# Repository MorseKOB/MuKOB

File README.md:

# MuKOB (μKOB) - Micro-controller based MorseKOB Client Device

Raspberry Pi Pico W (RP2040 CPU) based device with a built-in display and
a terminal interface. Uses built-in wifi to connect to the MorseKOB Server.

It interfaces to a KOB, Key + Sounder, Key + Tone, Paddle + Tone, etc. to provide Morse
input and output. The device can operate completely stand-alone (using the
display-touchscreen) or it can connect to a VT-220 terminal (or emulator like Putty)
to provide a larger interface and allow keyboard input.

It supports both American (railroad) and International code with sounder or tone
output, and allows use of Farnsworth word/character timing to promote improving
copying speed.

This repo also includes the **MuKOB Interface** which can be used with **MKOB** and **MorseKOB** through a USB to a PC.

# References
* [MorseKOB Main Project](https://github.com/MorseKOB)
* [PyKOB - The full/computer MKOB Client Application, utilities and Python libraries](https://github.com/MorseKOB/PyKOB)
* [Raspberry Pi Pico W](https://www.raspberrypi.com/documentation/microcontrollers/raspberry-pi-pico.html)
* [FatFs - Generic FAT Filesystem Module](http://elm-chan.org/fsw/ff/00index_e.html)
* [no-OS-FatFS-SD-SPI-RPi-Pico](https://github.com/carlk3/no-OS-FatFS-SD-SPI-RPi-Pico)

# Acknowledgements
The first, and probably most significant acknowledgement has to go to the architects, developers, technical writers, and other staff members responsible for the **Raspberry Pi Pico** and **Pico W**, the **Raspberry Pi Pico C/C++ SDK**, and the **Raspberry Pi Pico C/C++ Samples**.

This application implements a 'C' version of the American Morse encoding and decoding algorithms developed by *Les Kerr*.

The FAT file system and SD card libraries, with some small modifications (to configure for the MuKOB board and remove some printing), are from *ChaN* and *Carl Kugler* respectively.

As with every significant C project I've undertaken since the early '80s, my 'go-to' reference is **The C Programming Language** by *Brian Kernighan* and *Dennis Ritchie* (Prentice Hall, 1978 & 1988).

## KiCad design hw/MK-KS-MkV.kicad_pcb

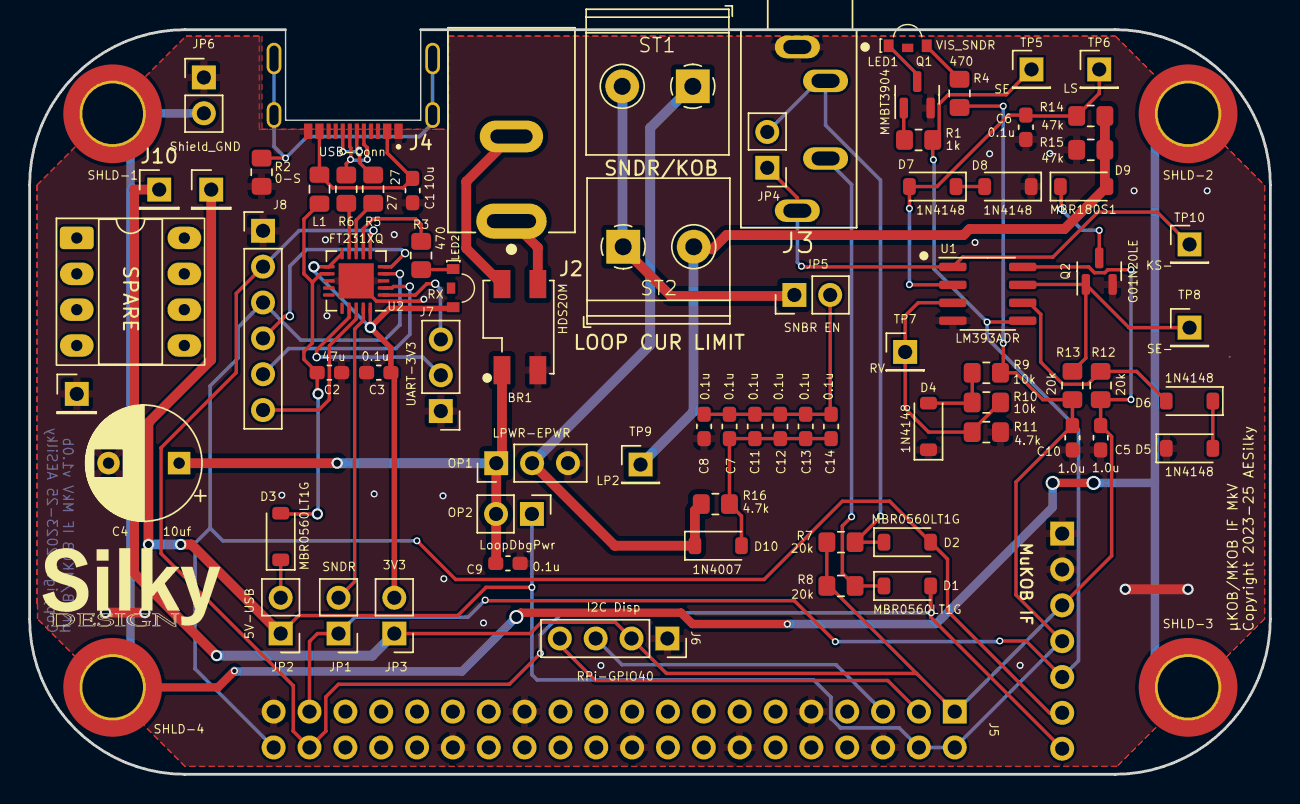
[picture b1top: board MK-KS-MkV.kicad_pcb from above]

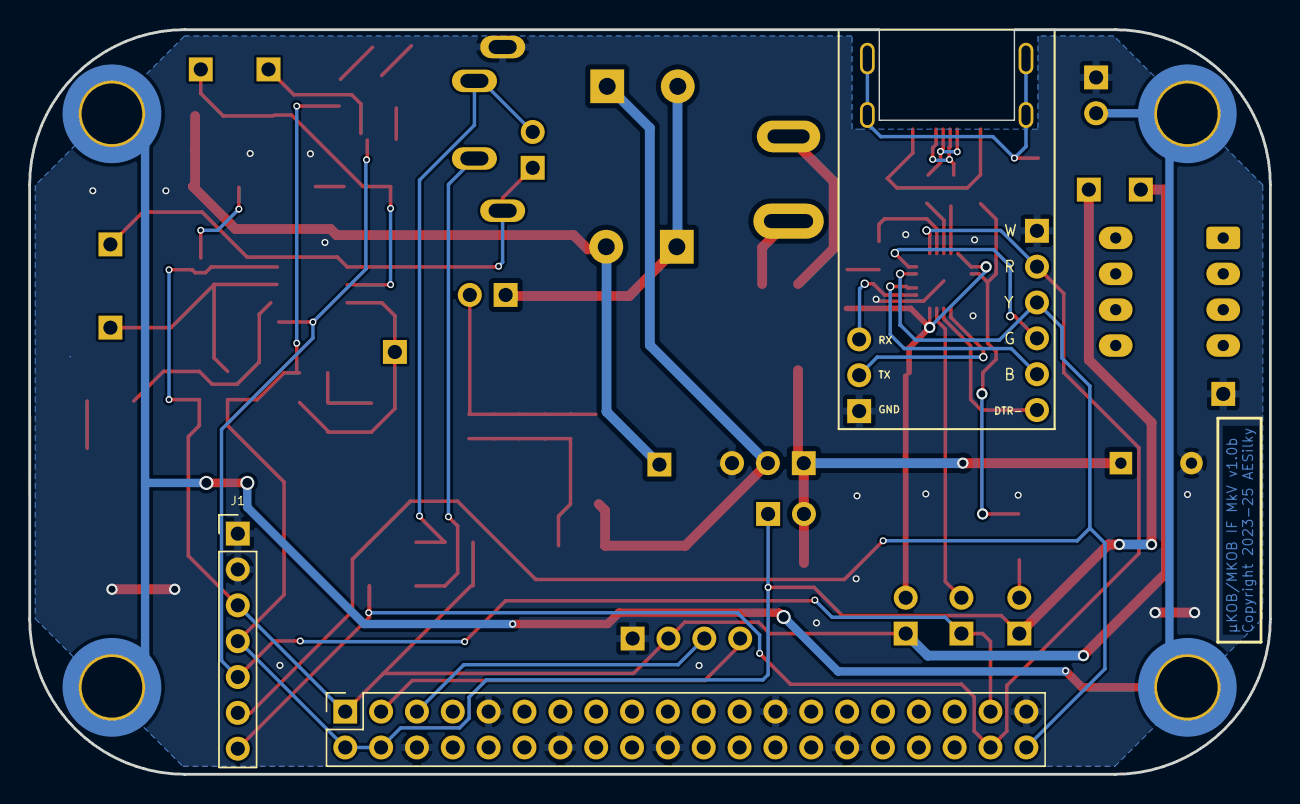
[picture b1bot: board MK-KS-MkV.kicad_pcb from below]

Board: 2 copper layers, 87.9 x 52.8 mm, 79 parts (2 on the bottom side), 48 nets.

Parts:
BR1: HDS20M; AES-BridgeRect-HDS20M-13-1KV-2A
C1: 10u; C_0603_1608Metric_Pad1.08x0.95mm_HandSolder
C2: 47u; C_0603_1608Metric_Pad1.08x0.95mm_HandSolder
C3, C6, C7, C8, C9, C11, C12, C13, C14: 0.1u; C_0603_1608Metric_Pad1.08x0.95mm_HandSolder
C4: 10uf; CP_Radial_D8.0mm_P5.00mm
C5, C10: 1.0u; C_0603_1608Metric_Pad1.08x0.95mm_HandSolder
D1, D2, D3: MBR0560LT1G; D_SOD-123
D4, D5, D6, D7, D8: 1N4148; D_SOD-123
D9: MBR180S1; D_SOD-123
D10: 1N4007; D_SOD-123
J1: MuKOB IF; PinHeader_1x07_P2.54mm_Vertical
J2: LOOP PWR; AES-CUI_PJ-037B
J3: KEY-PADDLE-1_8; AES-CUI_SJ1-3534NG-audio-jack
J4: USB-Conn; AES-USB_C_Amphenol_GSB1C4621DSHR
J5: RPi-GPIO40; PinSocket_2x20_P2.54mm_Vertical
J6: I2C Disp; PinSocket_1x04_P2.54mm_Vertical
J7: UART-3V3; PinHeader_1x03_P2.54mm_Vertical
J8: Selector-SW; PinHeader_1x06_P2.54mm_Vertical
J9, J10, J11: HDR 1x01 Pin; PinHeader_1x01_P2.54mm_Vertical
JP1: SNDR; PinHeader_1x02_P2.54mm_Vertical
JP2: 5V-USB; PinHeader_1x02_P2.54mm_Vertical
JP3: 3V3; PinHeader_1x02_P2.54mm_Vertical
JP4: KeyJack-NP; PinHeader_1x02_P2.54mm_Vertical
JP5: SNBR EN; PinHeader_1x02_P2.54mm_Vertical
JP6: Shield_GND; PinHeader_1x02_P2.54mm_Vertical
L1: 600RJ0.5A; L_0805_2012Metric_Pad1.15x1.40mm_HandSolder
LED1: VIS_SNDR; AES-LED_SMD_SIDEVIEW_Harvatek
LED2: RX; AES-LED_SMD_SIDEVIEW_Harvatek
OP1: LPWR-EPWR; PinHeader_1x03_P2.54mm_Vertical
OP2: LoopDbgPwr; PinHeader_1x02_P2.54mm_Vertical
Q1: MMBT3904; SOT-23
Q2: G01N20LE; SOT-23
R1: 1k; R_0805_2012Metric_Pad1.20x1.40mm_HandSolder
R2: 0-S; R_0805_2012Metric_Pad1.20x1.40mm_HandSolder
R3, R4: 470; R_0805_2012Metric_Pad1.20x1.40mm_HandSolder
R5, R6: 27; R_0805_2012Metric_Pad1.20x1.40mm_HandSolder
R7, R8, R12, R13: 20k; R_0805_2012Metric_Pad1.20x1.40mm_HandSolder
R9, R10: 10k; R_0805_2012Metric_Pad1.20x1.40mm_HandSolder
R11, R16: 4.7k; R_0805_2012Metric_Pad1.20x1.40mm_HandSolder
R14, R15: 47k; R_0805_2012Metric_Pad1.20x1.40mm_HandSolder
SHLD-1, SHLD-2, SHLD-3, SHLD-4: MountingHole_Pad; MountingHole_4.3mm_M4_ISO14580_Pad_TopBottom
ST1: SNDR/KOB; AES-TermBlock-2POS-5mm-Horz
ST2: LOOP CUR LIMIT; AES-TermBlock-2POS-5mm-Horz
TP5: SE; PinHeader_1x01_P2.54mm_Vertical
TP6: LS; PinHeader_1x01_P2.54mm_Vertical
TP7: RV; PinHeader_1x01_P2.54mm_Vertical
TP8: SE-; PinHeader_1x01_P2.54mm_Vertical
TP9: LP2; PinHeader_1x01_P2.54mm_Vertical
TP10: KS-; PinHeader_1x01_P2.54mm_Vertical
U1: LM393ADR; SOIC-8_3.9x4.9mm_P1.27mm
U2: FT231XQ; QFN-20-1EP_4x4mm_P0.5mm_EP2.5x2.5mm

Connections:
+3.3V: C5.2, J1.3, J5.1 (P3V3), J6.2, J10.1, JP3.1 (A), R7.2, R8.2, R12.1, U1.8 (VCC)
+5V: C10.2, J1.4, J5.2 (P5V), J5.4 (P5V), J9.1, JP2.1 (A), OP2.1, R4.1, R9.2, R13.2
/DASH-: D1.2 (A), J1.7, J5.38 (BCM20), J8.2, U2.6 (~CTS)
/DCD-: J8.4, U2.5 (~DCD)
/DOT-: D2.2 (A), J1.6, J5.40 (BCM21), J8.3, U2.4 (~DSR)
/DTR-: J8.6, U2.18 (~DTR)
/KEY_PDL_DOT-: D2.1 (K), J3.2, JP4.2 (B), R7.1
/KOB_KEY-: J3.4, JP4.1 (A), TP10.1, U1.1 (1OUT)
/LOOP_PWR: D10.1 (K), OP1.2 (C), R16.1, ST1.1
/LOOP_STATE: C6.1, D7.2 (A), R14.2, TP6.1, U1.2
/LP1: JP5.1 (A), ST1.2, ST2.1
/LP2: D9.2 (A), R14.1, R15.2, ST2.2, TP9.1
/LPI_A: BR1.4 (A), J2.1 (In)
/LPI_B: BR1.2 (A), J2.2 (Ext)
/LPI_P: BR1.1 (+), C4.1, C9.1, OP1.1 (A), OP2.2
/OFFSET_REF_V: R10.1, R11.2, TP7.1, U1.3
/PDL_DASH-: D1.1 (K), J3.3, R8.1
/RI-: J8.5, U2.2 (~RI)
/RTS: JP1.2 (B), U2.19 (~RTS)
/SCL: J5.5 (BCM3), J6.3
/SDA: J5.3 (BCM2), J6.4
/SNDR_EN: J1.5, J5.37 (BCM26), JP1.1 (A), R1.1, TP5.1, U1.5 (2IN+)
/SNDR_EN-: Q2.1 (G), R13.1, TP8.1, U1.7 (2OUT)
/V3.3I: C3.1, JP3.2 (B), LED2.2 (A), U2.10 (3V3OUT), U2.11 (~RESET), U2.20 (VCCIO)
/V5I: C2.2, D3.2 (A), L1.2, U2.12 (VCC)
Earth: JP6.2 (B), SHLD-1.1, SHLD-2.1, SHLD-3.1, SHLD-4.1
GND: BR1.3 (-), C1.1, C2.1, C3.2, C4.2, C5.1, C6.2, C8.2, C9.2, C10.1, D4.1 (K), D5.1 (K), D8.1 (K), J1.1, J1.2, J3.1, J4.A1_B12 (GND), J4.B1_A12 (GND), J5.6 (GND), J5.9 (GND), J5.14 (GND), J5.20 (GND), J5.25 (GND), J5.30 (GND), J5.39 (GND), J6.1, J7.1, J8.1, J11.1, JP6.1 (A), OP1.3 (B), Q1.2 (E), Q2.2 (S), R2.1, R11.1, R15.1, U1.4 (GND), U2.3 (GND), U2.13 (GND), U2.21 (GND)
unnamed: C1.2, J4.A4_B9 (VBUS), J4.B4_A9 (VBUS), L1.1
unnamed: D3.1 (K), JP2.2 (B)
unnamed: D4.2 (A), R9.1, R10.2
unnamed: D5.2 (A), D6.1 (K)
unnamed: D6.2 (A), R12.2, U1.6 (2IN-)
unnamed: D7.1 (K), D8.2 (A)
unnamed: D9.1 (K), Q2.3 (D)
unnamed: C7.1, C11.1, C12.1, C13.1, C14.1, D10.2 (A), R16.2
unnamed: J4.A6 (D+), J4.B6 (D+), R5.1
unnamed: J4.A7 (D-), J4.B7 (D-), R6.1
unnamed: J4.SH1 (SHIELD), J4.SH2 (SHIELD), J4.SH3 (SHIELD), J4.SH4 (SHIELD), R2.2
unnamed: J7.2, U2.17 (TXD)
unnamed: J7.3, U2.1 (RXD)
unnamed: C7.2, C8.1, C11.2, C12.2, C13.2, C14.2, JP5.2 (B)
unnamed: LED1.2 (A), R4.2
unnamed: LED1.1 (K), Q1.3 (C)
unnamed: LED2.1 (K), R3.1
unnamed: Q1.1 (B), R1.2
unnamed: R3.2, U2.7 (CBUS2)
unnamed: R6.2, U2.9 (USBDM)
unnamed: R5.2, U2.8 (USBDP)

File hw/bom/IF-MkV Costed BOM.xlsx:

Item | Sourced | Placed | References | Value | Footprint | Quantity Total | Cost Each | Base | Base Cost | Key Jack 1/8 | K18 Cost | Sndr/Loop Power | SLPS Cost | LED (Vis) Sounder | L(VS) Cost | RPi Conn | RPC Cost | Debug Only | (qty check)
1 |  |  | C3, C6, C7, C8, C9, C11, C12, C13, C14 | 0.1u | C_0603_1608Metric_Pad1.08x0.95mm_HandSolder | 9 | 0.02 | 8 | 0.16 |  | 0 | 1 | 0.02 |  | 0 | -1 | -0.02 |  | 9
2 |  |  | C5, C10 | 1.0u | C_0603_1608Metric_Pad1.08x0.95mm_HandSolder | 2 | 0.02 | 2 | 0.04 |  | 0 |  | 0 |  | 0 |  | 0 |  | 2
3 |  |  | C1 | 10u | C_0603_1608Metric_Pad1.08x0.95mm_HandSolder | 1 | 0.02 | 1 | 0.02 |  | 0 |  | 0 |  | 0 | -1 | -0.02 |  | 1
4 |  |  | C2 | 47u | C_0603_1608Metric_Pad1.08x0.95mm_HandSolder | 1 | 0.05 | 1 | 0.05 |  | 0 |  | 0 |  | 0 | -1 | -0.05 |  | 1
5 |  |  | C4 | 10uf | CP_Radial_D8.0mm_P5.00mm | 1 | 1.5 | 0 | 0 |  | 0 | 1 | 1.5 |  | 0 |  | 0 |  | 1
6 |  |  | R7, R8, R12, R13 | 20k | R_0805_2012Metric_Pad1.20x1.40mm_HandSolder | 4 | 0.03 | 4 | 0.12 |  | 0 |  | 0 |  | 0 |  | 0 |  | 4
7 |  |  | R3, R4 | 470 | R_0805_2012Metric_Pad1.20x1.40mm_HandSolder | 1 | 0.03 | 0 | 0 |  | 0 |  | 0 | 1 | 0.03 |  | 0 |  | 1
8 |  |  | R5, R6 | 27 | R_0805_2012Metric_Pad1.20x1.40mm_HandSolder | 2 | 0.03 | 2 | 0.06 |  | 0 |  | 0 |  | 0 | -2 | -0.06 |  | 2
9 |  |  | R9, R10 | 10k | R_0805_2012Metric_Pad1.20x1.40mm_HandSolder | 2 | 0.03 | 2 | 0.06 |  | 0 |  | 0 |  | 0 |  | 0 |  | 2
10 |  |  | R11, R16 | 4.7k | R_0805_2012Metric_Pad1.20x1.40mm_HandSolder | 2 | 0.03 | 2 | 0.06 |  | 0 |  | 0 |  | 0 |  | 0 |  | 2
11 |  |  | R14, R15 | 47k | R_0805_2012Metric_Pad1.20x1.40mm_HandSolder | 2 | 0.03 | 2 | 0.06 |  | 0 |  | 0 |  | 0 |  | 0 |  | 2
12 |  |  | R1 | 1k | R_0805_2012Metric_Pad1.20x1.40mm_HandSolder | 1 | 0.03 | 0 | 0 |  | 0 |  | 0 | 1 | 0.03 |  | 0 |  | 1
13 |  |  | R2 | 0-S | R_0805_2012Metric_Pad1.20x1.40mm_HandSolder | 1 | 0.03 | 1 | 0.03 |  | 0 |  | 0 |  | 0 | -1 | -0.03 |  | 1
14 |  |  | L1 | 600RJ0.5A | L_0805_2012Metric_Pad1.15x1.40mm_HandSolder | 1 | 0.15 | 1 | 0.15 |  | 0 |  | 0 |  | 0 |  | 0 |  | 1
15 |  |  | D4, D5, D6, D7, D8 | 1N4148 | D_SOD-123 | 5 | 0.05 | 5 | 0.25 |  | 0 |  | 0 |  | 0 |  | 0 |  | 5
16 |  |  | D1, D2, D3 | MBR0560LT1G | D_SOD-123 | 3 | 0.15 | 3 | 0.44999999999999996 |  | 0 |  | 0 |  | 0 |  | 0 |  | 3
17 |  |  | D9 | MBR180S1 | D_SOD-123 | 1 | 0.15 | 1 | 0.15 |  | 0 |  | 0 |  | 0 |  | 0 |  | 1
18 |  |  | D10 | 1N4007 | D_SOD-123 | 1 | 0.08 | 1 | 0.08 |  | 0 |  | 0 |  | 0 |  | 0 |  | 1
19 |  |  | U1 | LM393ADR | SOIC-8_3.9x4.9mm_P1.27mm | 1 | 0.5 | 1 | 0.5 |  | 0 |  | 0 |  | 0 |  | 0 |  | 1
20 |  |  | U2 | FT231XQ | QFN-20-1EP_4x4mm_P0.5mm_EP2.5x2.5mm | 1 | 3.5 | 1 | 3.5 |  | 0 |  | 0 |  | 0 | -1 | -3.5 |  | 1
21 |  |  | BR1 | HDS20M | AES-BridgeRect-HDS20M-13-1KV-2A | 1 | 0.3 | 0 | 0 |  | 0 | 1 | 0.3 |  | 0 |  | 0 |  | 1
22 |  |  | JP4 | KeyJack-NP | PinHeader_1x02_P2.54mm_Vertical | 1 | 0.01 | 1 | 0.01 |  | 0 |  | 0 |  | 0 |  | 0 |  | 1
23 |  |  | JP5 | SNBR EN | PinHeader_1x02_P2.54mm_Vertical | 1 | 0.01 | 1 | 0.01 |  | 0 |  | 0 |  | 0 |  | 0 |  | 1
24 |  |  | JP6 | Shield-GND | PinHeader_1x02_P2.54mm_Vertical | 1 | 0.01 | 1 | 0.01 |  | 0 |  | 0 |  | 0 |  | 0 |  | 1
25 |  |  | LED1 | VIS_SNDR | AES-LED_SMD_SIDEVIEW_Harvatek | 1 | 0.1 | 0 | 0 |  | 0 |  | 0 | 1 | 0.1 |  | 0 |  | 1
26 |  |  | LED2 | RX | AES-LED_SMD_SIDEVIEW_Harvatek | 0 | 0.1 | 0 | 0 |  | 0 |  | 0 |  | 0 |  | 0 |  | 0
27 |  |  | OP1 | LPWR-EPWR | PinHeader_1x03_P2.54mm_Vertical | 1 | 0.03 | 0 | 0 |  | 0 | 1 | 0.03 |  | 0 |  | 0 |  | 1
28 |  |  | Q1 | MMBT3904 | SOT-23 | 1 | 0.04 | 0 | 0 |  | 0 |  | 0 | 1 | 0.04 |  | 0 |  | 1
29 |  |  | Q2 | G01N20LE | SOT-23 | 1 | 0.35 | 1 | 0.35 |  | 0 |  | 0 |  | 0 |  | 0 |  | 1
30 |  |  | ST1 | SNDR/KOB | AES-TermBlock-2POS-5mm-Horz | 1 | 0.35 | 1 | 0.35 |  | 0 |  | 0 |  | 0 |  | 0 |  | 1
31 |  |  | ST2 | LOOP CUR LIMIT | AES-TermBlock-2POS-5mm-Horz | 1 | 0.35 | 1 | 0.35 |  | 0 |  | 0 |  | 0 |  | 0 |  | 1
32 |  |  | J2 | LOOP PWR | AES-CUI_PJ-037B | 1 | 0.7 | 0 | 0 |  | 0 | 1 | 0.7 |  | 0 |  | 0 |  | 1
33 |  |  | J3 | KEY-PADDLE-1_8 | AES-CUI_SJ1-3534NG-audio-jack | 1 | 1.5 | 0 | 0 | 1 | 1.5 |  | 0 |  | 0 |  | 0 |  | 1
34 |  |  | J4 | USB-Conn | AES-USB_C_Amphenol_GSB1C4621DSHR | 1 | 0.5 | 1 | 0.5 |  | 0 |  | 0 |  | 0 | -1 | -0.5 |  | 1
35 |  |  | J5 | RPi-GPIO40 | 2x20 Socket Header | 1 | 3.5 | 0 | 0 |  | 0 |  | 0 |  | 0 | 1 | 3.5 |  | 0
36 |  |  | PCB | MuKOB IF MkV | PCBWay | 1 | 7.5 | 1 | 7.5 |  | 0 |  | 0 |  | 0 |  | 0 |  | 1
37 |  |  | Board Insulator | vinyl | Cricut | 2 | 1 | 2 | 2 |  | 0 |  | 0 |  | 0 | -1 | -1 |  | 2
38 |  |  | Shield | Altoids Tin | (Modifications) | 1 | 4 | 1 | 4 |  | 0 |  | 0 |  | 0 |  | 0 |  | 1
39 |  |  | Connector Faceplate | MkV Face | Spring-Steel SendCutSend | 1 | 1 | 1 | 1 |  | 0 |  | 0 |  | 0 | -1 | -1 |  | 1
40 |  |  | Mounting Hardware |  | #6 SS Screws, washers, nuts (set) | 1 | 2 | 1 | 2 |  | 0 |  | 0 |  | 0 | -1 | -2 |  | 1
 |  |  |  |  |  |  |  |  | 0 |  | 0 |  | 0 |  | 0 |  | 0 |  | 0
 |  |  |  |  | Totals | 62 |  | 51 | 23.82 | 1 | 1.5 | 5 | 2.5499999999999998 | 4 | 0.2 | -10 | -4.68 | 0 | 1
 |  |  |  | 'Full' (Non-RPi) >>> | Base + 1/8" Key Jack + Sndr Pwr + LED(VisSndr) |  | 28.07
 |  |  |  | 'LoopPwr' (Non-RPi) >>> | Base + Sndr Pwr |  | 26.37
 |  |  |  | 'Minimum' (Non-RPi) >>> | Base Only (No: Key Jack, Power, LED) |  | 23.82

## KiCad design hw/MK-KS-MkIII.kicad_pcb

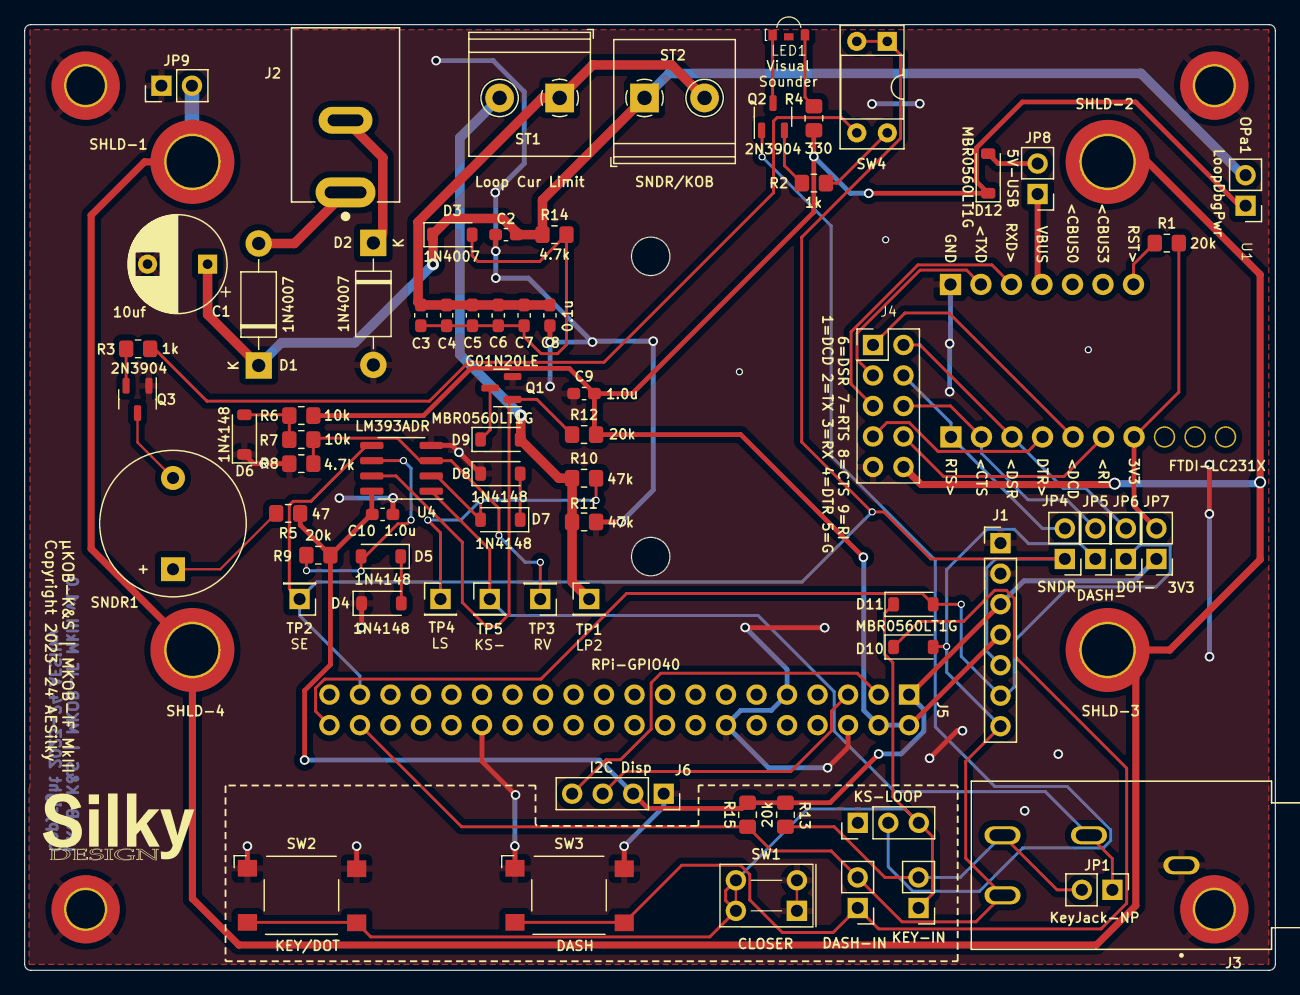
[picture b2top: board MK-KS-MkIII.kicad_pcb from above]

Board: 2 copper layers, 104.1 x 78.7 mm, 81 parts (1 on the bottom side), 48 nets.

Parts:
C1: 10uf; CP_Radial_D8.0mm_P5.00mm
C2, C3, C4, C5, C6, C7, C8: 0.1u; C_0603_1608Metric_Pad1.08x0.95mm_HandSolder
C9, C10: 1.0u; C_0603_1608Metric_Pad1.08x0.95mm_HandSolder
D1, D2: 1N4007; D_DO-41_SOD81_P10.16mm_Horizontal
D3: 1N4007; D_SOD-123
D4, D5, D6, D7, D8: 1N4148; D_SOD-123
D9, D10, D11, D12: MBR0560LT1G; D_SOD-123
G1: LOGO; SILKY-DESIGN-logo-0_50-AES
J1: MuKOB IF; PinHeader_1x07_P2.54mm_Vertical
J2: LOOP PWR; AES-CUI_PJ-037B
J3: KEY-PADDLE; AES-CUI_SJ-63063B-audio-jack
J4: COMM-DCE-10; PinHeader_2x05_DB9-Order
J5: RPi-GPIO40; PinSocket_2x20_P2.54mm_Vertical
J6: I2C Disp; PinSocket_1x04_P2.54mm_Vertical
JP1, JP9: KeyJack-NP; PinHeader_1x02_P2.54mm_Vertical
JP2: KEY-IN; PinHeader_1x02_P2.54mm_Vertical
JP3: DASH-IN; PinHeader_1x02_P2.54mm_Vertical
JP4: SNDR; PinHeader_1x02_P2.54mm_Vertical
JP5: DASH-; PinHeader_1x02_P2.54mm_Vertical
JP6: DOT-; PinHeader_1x02_P2.54mm_Vertical
JP7: 3V3; PinHeader_1x02_P2.54mm_Vertical
JP8: 5V-USB; PinHeader_1x02_P2.54mm_Vertical
LED1: SNDR; AES-LED_SMD_SIDEVIEW_Harvatek
M_KSI1, M_KSI2, M_KSI3, M_KSI4: MountingHole_Pad; MountingHole_3.2mm_M3_ISO7380_Pad_TopBottom
OP1: KS-LOOP; PinHeader_1x03_P2.54mm_Vertical
OPa1: LoopDbgPwr; PinHeader_1x02_P2.54mm_Vertical
Q1: G01N20LE; SOT-23
Q2, Q3: 2N3904; SOT-23-3
R1, R9, R12, R13, R15: 20k; R_0805_2012Metric_Pad1.20x1.40mm_HandSolder
R2, R3: 1k; R_0805_2012Metric_Pad1.20x1.40mm_HandSolder
R4: 330; R_0805_2012Metric_Pad1.20x1.40mm_HandSolder
R5: 47; R_0805_2012Metric_Pad1.20x1.40mm_HandSolder
R6, R7: 10k; R_0805_2012Metric_Pad1.20x1.40mm_HandSolder
R8, R14: 4.7k; R_0805_2012Metric_Pad1.20x1.40mm_HandSolder
R10, R11: 47k; R_0805_2012Metric_Pad1.20x1.40mm_HandSolder
SHLD-1, SHLD-2, SHLD-3, SHLD-4: MountingHole_Pad; MountingHole_4.3mm_M4_ISO14580_Pad_TopBottom
SNDR1: Buzzer; Buzzer_12x9.5RM7.6
ST1: Loop Cur Limit; TerminalBlock_Philmore_TB132_1x02_P5.00mm_Horizontal
ST2: SNDR/KOB; TerminalBlock_Philmore_TB132_1x02_P5.00mm_Horizontal
SW1: CLOSER; AES-SW-TGL-Micro-DPST-CIT
SW2: KEY/DOT; AES-SW_PUSH_SMD_1P1T_NO_6x6mm
SW3: DASH; AES-SW_PUSH_SMD_1P1T_NO_6x6mm
SW4: SW_DIP_x02; DIP-4_W7.62mm_Socket
TP1: LP2; PinHeader_1x01_P2.54mm_Vertical
TP2: SE; PinHeader_1x01_P2.54mm_Vertical
TP3: RV; PinHeader_1x01_P2.54mm_Vertical
TP4: LS; PinHeader_1x01_P2.54mm_Vertical
TP5: KS-; PinHeader_1x01_P2.54mm_Vertical
U1: FTDI-LC231X; AES-FTDI_LC231X
U4: LM393ADR; SOIC-8_3.9x4.9mm_P1.27mm

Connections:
+3.3V: C10.2, J1.3, J5.1 (P3V3), J6.2, JP7.1 (A), R5.1, R9.1, R13.2, R15.2, U4.8 (VCC)
+5V: C9.2, D12.1 (K), J1.4, J5.2 (P5V), J5.4 (P5V), OPa1.1, R4.1, R6.2, R12.2
/BZ+: R5.2, SNDR1.1 (-)
/BZ-: Q3.3 (C), SNDR1.2 (+)
/CTS: J4.8, JP5.2 (B), U1.2R (CTS)
/DASH-: D10.1 (K), JP3.1 (A), SW3.2
/DOT-: D11.1 (K), JP2.1 (A), OP1.3 (B), SW1.2 (B), SW2.2
/DSR: J4.6, JP6.2 (B), U1.3R (DSR)
/DTR: J4.4, U1.4R (DTR)
/KEY_PDL-: J3.2, JP1.2 (B), JP2.2 (B), R13.1
/KEY_PDL_DOT-: D11.2 (A), J1.6, J5.40 (BCM21), JP6.1 (A)
/KOB_KEY-: J3.4, JP1.1 (A), TP5.1, U4.1 (1OUT)
/LOOP_PWR: C1.1, C2.1, D1.1 (K), D3.1 (K), OPa1.2, R14.1, ST2.1
/LOOP_STATE: D7.2 (A), R10.2, TP4.1, U4.2
/LP1: C3.2, C4.2, C5.2, C6.2, C7.2, C8.1, ST1.1, ST2.2
/LP2: D9.2 (A), R10.1, R11.2, ST1.2, TP1.1
/LPI+: D1.2 (A), J2.1 (In)
/LPI-: D2.1 (K), J2.2 (Ext)
/OFFSET_REF_V: R7.1, R8.2, TP3.1, U4.3
/PDL_DASH-: D10.2 (A), J1.7, J3.3, J5.38 (BCM20), JP3.2 (B), JP5.1 (A), R15.1
/RESET-: R1.1, U1.7L (Reset#)
/RI: J4.9, U1.6R (RI)
/RTS: J4.7, JP4.2 (B), U1.1R (RTS)
/RXD: J4.3, U1.3L (RXD)
/SCL: J5.5 (BCM3), J6.3
/SDA: J5.3 (BCM2), J6.4
/SEB: R3.1, SW4.3
/SEL: R2.1, SW4.4
/SLG: OP1.2 (C), Q2.1 (E)
/SNDR_EN: J1.5, J5.37 (BCM26), JP4.1 (A), SW4.1, SW4.2, TP2.1, U4.5 (2IN+)
/SNDR_EN-: Q1.1 (G), R12.1, U4.7 (2OUT)
/TXD: J4.2, U1.2L (TXD)
/V3.3I: JP7.2 (B), R1.2, U1.7R (3V3)
/V5I: D12.2 (A), JP8.2 (B)
/VBUS: JP8.1 (A), U1.4L (VBUS)
Earth: J4.10, JP9.2 (B), SHLD-1.1, SHLD-2.1, SHLD-3.1, SHLD-4.1
GND: C1.2, C2.2, C8.2, C9.1, C10.1, D2.2 (A), D4.1 (K), D6.1 (K), D8.1 (K), J1.1, J1.2, J3.1, J4.5, J5.6 (GND), J5.9 (GND), J5.14 (GND), J5.20 (GND), J5.25 (GND), J5.30 (GND), J5.39 (GND), J6.1, JP9.1 (A), M_KSI1.1, M_KSI2.1, M_KSI3.1, M_KSI4.1, OP1.1 (A), Q1.2 (S), Q3.1 (E), R8.1, R11.1, SW1.1 (A), SW2.1, SW3.1, U1.1L (GND), U4.4 (GND)
unnamed: C3.1, C4.1, C5.1, C6.1, C7.1, D3.2 (A), R14.2
unnamed: D4.2 (A), D5.1 (K)
unnamed: D5.2 (A), R9.2, U4.6 (2IN-)
unnamed: D6.2 (A), R6.1, R7.2
unnamed: D7.1 (K), D8.2 (A)
unnamed: D9.1 (K), Q1.3 (D)
unnamed: J4.1, U1.5R (DCD)
unnamed: LED1.2 (A), R4.2
unnamed: LED1.1 (K), Q2.3 (C)
unnamed: Q2.2 (B), R2.2
unnamed: Q3.2 (B), R3.2

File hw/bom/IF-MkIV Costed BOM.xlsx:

Item | Sourced | Placed | References | Value | Footprint | Quantity Total | Cost Each | Base | Base Cost | Key Jack 1/4 | K14 Cost | Key Jack 1/8 | K18 Cost | Sndr/Loop Power | SLPS Cost | LED+Mini Sounder | L/MS Cost | Test Key Switches | TKS Cost | RPi Conn | RPC Cost | Debug Only | (qty check)
1 |  |  | C2, C3, C4, C5, C6, C7, C8, C11 | 0.1u | C_0603_1608Metric_Pad1.08x0.95mm_HandSolder | 8 | 0.02 | 8 | 0.16 |  | 0 |  | 0 |  | 0 |  | 0 |  | 0 |  | 0 |  | 0
2 |  |  | C9, C10 | 1.0u | C_0603_1608Metric_Pad1.08x0.95mm_HandSolder | 2 | 0.02 | 2 | 0.04 |  | 0 |  | 0 |  | 0 |  | 0 |  | 0 |  | 0 |  | 0
3 |  |  | C1 | 10uf | CP_Radial_D8.0mm_P5.00mm | 1 | 1.4 | 1 | 1.4 |  | 0 |  | 0 |  | 0 |  | 0 |  | 0 |  | 0 |  | 0
4 |  |  | C12 | 10uf Tant | CP_EIA-3528-12_Kemet-T_Pad1.50x2.35mm_HandSolder | 1 | 0.13 | 0 | 0 |  | 0 |  | 0 | 0 | 0 | 1 | 0.13 |  | 0 |  | 0 |  | 0
5 |  |  | R1, R9, R12, R13, R15 | 20k | R_0805_2012Metric_Pad1.20x1.40mm_HandSolder | 5 | 0.02 | 5 | 0.1 |  | 0 |  | 0 |  | 0 |  | 0 |  | 0 |  | 0 |  | 0
6 |  |  | R6, R7 | 10k | R_0805_2012Metric_Pad1.20x1.40mm_HandSolder | 2 | 0.02 | 2 | 0.04 |  | 0 |  | 0 |  | 0 |  | 0 |  | 0 |  | 0 |  | 0
7 |  |  | R8, R14 | 4.7k | R_0805_2012Metric_Pad1.20x1.40mm_HandSolder | 2 | 0.02 | 2 | 0.04 |  | 0 |  | 0 |  | 0 |  | 0 |  | 0 |  | 0 |  | 0
8 |  |  | R10, R11 | 47k | R_0805_2012Metric_Pad1.20x1.40mm_HandSolder | 2 | 0.02 | 2 | 0.04 |  | 0 |  | 0 |  | 0 |  | 0 |  | 0 |  | 0 |  | 0
9 |  |  | R2 | 1k | R_0805_2012Metric_Pad1.20x1.40mm_HandSolder | 1 | 0.02 | 0 | 0 |  | 0 |  | 0 | 0 | 0 | 1 | 0.02 |  | 0 |  | 0 |  | 0
10 |  |  | R4 | 330 | R_0805_2012Metric_Pad1.20x1.40mm_HandSolder | 1 | 0.02 | 0 | 0 |  | 0 |  | 0 | 0 | 0 | 1 | 0.02 |  | 0 |  | 0 |  | 0
11 |  |  | R5 | 0|16 | R_0805_2012Metric_Pad1.20x1.40mm_HandSolder | 1 | 0.02 | 0 | 0 |  | 0 |  | 0 | 0 | 0 | 1 | 0.02 |  | 0 |  | 0 |  | 0
12 |  |  | D4, D5, D6, D7, D8 | 1N4148 | D_SOD-123 | 5 | 0.05 | 5 | 0.25 |  | 0 |  | 0 |  | 0 |  | 0 |  | 0 |  | 0 |  | 0
13 |  |  | D2, D10, D11, D12 | MBR0560LT1G | D_SOD-123 | 4 | 0.12 | 3 | 0.36 |  | 0 |  | 0 |  | 0 | 1 | 0.12 |  | 0 |  | 0 |  | 0
14 |  |  | D1 | HDS20M | TO-269AA | 1 | 0.3 | 0 | 0 |  | 0 |  | 0 | 1 | 0.3 |  | 0 |  | 0 |  | 0 |  | 0
15 |  |  | D3 | 1N4007 | D_SOD-123 | 1 | 0.08 | 1 | 0.08 |  | 0 |  | 0 |  | 0 |  | 0 |  | 0 |  | 0 |  | 0
16 |  |  | D9 | MBR180S1 (Sndr Drv) | D_SOD-123 | 1 | 0.12 | 1 | 0.12 |  | 0 |  | 0 |  | 0 |  | 0 |  | 0 |  | 0 |  | 0
17 |  |  | U1 | FTDI-LC231X | AES-FTDI_LC231X | 1 | 9.75 | 1 | 9.75 |  | 0 |  | 0 |  | 0 |  | 0 |  | 0 |  | 0 |  | 0
18 |  |  | U4 | LM393ADR | SOIC-8_3.9x4.9mm_P1.27mm | 1 | 0.4 | 1 | 0.4 |  | 0 |  | 0 |  | 0 |  | 0 |  | 0 |  | 0 |  | 0
19 |  |  | SW1 | CLOSER | AES-SW-TGL-Micro-DPST-CIT | 1 | 2.6 | 0 | 0 |  | 0 |  | 0 |  | 0 |  | 0 | 1 | 2.6 |  | 0 |  | 0
20 |  |  | SW2 | KEY/DOT | AES-SW_PUSH_SMD_1P1T_NO_6x6mm | 1 | 0.55000000000000004 | 0 | 0 |  | 0 |  | 0 |  | 0 |  | 0 | 1 | 0.55000000000000004 |  | 0 |  | 0
21 |  |  | SW3 | DASH | AES-SW_PUSH_SMD_1P1T_NO_6x6mm | 1 | 0.55000000000000004 | 0 | 0 |  | 0 |  | 0 |  | 0 |  | 0 | 1 | 0.55000000000000004 |  | 0 |  | 0
22 |  |  | SW4 | SW_DIP_x02 | DIP-4_W7.62mm_Socket | 1 | 1.5 | 0 | 0 |  | 0 |  | 0 |  | 0 | 1 | 1.5 |  | 0 |  | 0 |  | 0
23 |  |  | JP8, JP10 | 5V-USB | PinHeader_1x02_P2.54mm_Vertical | 2 | 0.01 | 2 | 0.02 |  | 0 |  | 0 |  | 0 |  | 0 |  | 0 |  | 0 |  | 0
24 |  |  | JP1 | KeyJack-NP | PinHeader_1x02_P2.54mm_Vertical | 1 | 0.01 | 1 | 0.01 |  | 0 |  | 0 |  | 0 |  | 0 |  | 0 |  | 0 |  | 0
25 |  |  | JP2 | KEY-IN | PinHeader_1x02_P2.54mm_Vertical | 1 | 0.01 | 1 | 0.01 |  | 0 |  | 0 |  | 0 |  | 0 |  | 0 |  | 0 |  | 0
26 |  |  | JP3 | DASH-IN | PinHeader_1x02_P2.54mm_Vertical | 1 | 0.01 | 1 | 0.01 |  | 0 |  | 0 |  | 0 |  | 0 |  | 0 |  | 0 |  | 0
27 |  |  | JP4 | SNDR | PinHeader_1x02_P2.54mm_Vertical | 1 | 0.01 | 1 | 0.01 |  | 0 |  | 0 |  | 0 |  | 0 |  | 0 |  | 0 |  | 0
28 |  |  | JP5 | DASH- | PinHeader_1x02_P2.54mm_Vertical | 1 | 0.01 | 1 | 0.01 |  | 0 |  | 0 |  | 0 |  | 0 |  | 0 |  | 0 |  | 0
29 |  |  | JP6 | DOT- | PinHeader_1x02_P2.54mm_Vertical | 1 | 0.01 | 1 | 0.01 |  | 0 |  | 0 |  | 0 |  | 0 |  | 0 |  | 0 |  | 0
30 |  |  | JP7 | 3V3 | PinHeader_1x02_P2.54mm_Vertical | 1 | 0.01 | 1 | 0.01 |  | 0 |  | 0 |  | 0 |  | 0 |  | 0 |  | 0 |  | 0
31 |  |  | JP9 | Shield_GND | PinHeader_1x02_P2.54mm_Vertical | 1 | 0.01 | 1 | 0.01 |  | 0 |  | 0 |  | 0 |  | 0 |  | 0 |  | 0 |  | 0
32 |  |  | LED1 | VIS_SNDR | AES-LED_SMD_SIDEVIEW_Harvatek | 1 | 0.1 | 0 | 0 |  | 0 |  | 0 |  | 0 | 1 | 0.1 |  | 0 |  | 0 |  | 0
33 |  |  | OP1 | KS-LOOP | PinHeader_1x03_P2.54mm_Vertical | 1 | 0.02 | 0 | 0 |  | 0 |  | 0 |  | 0 | 1 | 0.02 |  | 0 |  | 0 |  | 0
34 |  |  | OPa1 | LoopDbgPwr | PinHeader_1x02_P2.54mm_Vertical | 1 | 0.01 | 1 | 0.01 |  | 0 |  | 0 |  | 0 |  | 0 |  | 0 |  | 0 |  | 0
35 |  |  | Q1 | G01N20LE (Sndr Drv) | SOT-23 | 1 | 0.35 | 1 | 0.35 |  | 0 |  | 0 |  | 0 |  | 0 |  | 0 |  | 0 |  | 0
36 |  |  | Q2 | MMBT3904 | SOT-23 | 1 | 0.04 | 0 | 0 |  | 0 |  | 0 |  | 0 | 1 | 0.04 |  | 0 |  | 0 |  | 0
37 |  |  | RLY1 | RELAY-5v|3v-DPST | Relay_SPDT_Finder_36.11 | 1 | 2 | 0 | 0 |  | 0 |  | 0 |  | 0 | 1 | 2 |  | 0 |  | 0 |  | 0
38 |  |  | ST1 | LOOP_CUR_LIMIT | TerminalBlock_Philmore_TB132_1x02_P5.00mm_Horizontal | 1 | 0.35 | 1 | 0.35 |  | 0 |  | 0 |  | 0 |  | 0 |  | 0 |  | 0 |  | 0
39 |  |  | ST2 | SNDR/KOB | TerminalBlock_Philmore_TB132_1x02_P5.00mm_Horizontal | 1 | 0.35 | 1 | 0.35 |  | 0 |  | 0 |  | 0 |  | 0 |  | 0 |  | 0 |  | 0
40 |  |  | TP1 | LP2 | PinHeader_1x01_P2.54mm_Vertical | 1 | 0 | 0 | 0 |  | 0 |  | 0 |  | 0 |  | 0 |  | 0 |  | 0 | 1 | 0
41 |  |  | TP2 | SE | PinHeader_1x01_P2.54mm_Vertical | 1 | 0 | 0 | 0 |  | 0 |  | 0 |  | 0 |  | 0 |  | 0 |  | 0 | 1 | 0
42 |  |  | TP3 | RV | PinHeader_1x01_P2.54mm_Vertical | 1 | 0 | 0 | 0 |  | 0 |  | 0 |  | 0 |  | 0 |  | 0 |  | 0 | 1 | 0
43 |  |  | TP4 | LS | PinHeader_1x01_P2.54mm_Vertical | 1 | 0 | 0 | 0 |  | 0 |  | 0 |  | 0 |  | 0 |  | 0 |  | 0 | 1 | 0
44 |  |  | TP5 | KS- | PinHeader_1x01_P2.54mm_Vertical | 1 | 0 | 0 | 0 |  | 0 |  | 0 |  | 0 |  | 0 |  | 0 |  | 0 | 1 | 0
45 |  |  | TP6 | SE- | PinHeader_1x01_P2.54mm_Vertical | 1 | 0 | 0 | 0 |  | 0 |  | 0 |  | 0 |  | 0 |  | 0 |  | 0 | 1 | 0
46 |  |  | J1 | MuKOB IF | PinHeader_1x07_P2.54mm_Vertical | 1 | 0.05 | 0 | 0 |  | 0 |  | 0 |  | 0 |  | 0 |  | 0 |  | 0 |  | 1
47 |  |  | J2 | LOOP PWR | AES-CUI_PJ-037B | 1 | 0.7 | 0 | 0 |  | 0 |  | 0 | 1 | 0.7 |  | 0 |  | 0 |  | 0 |  | 0
48 |  |  | J3 | KEY-PADDLE | AES-CUI_SJ-63063B-audio-jack | 1 | 1.8 | 0 | 0 | 1 | 1.8 |  | 0 |  | 0 |  | 0 |  | 0 |  | 0 |  | 0
49 |  |  | J4 | COMM-DCE-10 | PinHeader_2x05_DB9-Order | 1 | 0.1 | 0 | 0 |  | 0 |  | 0 |  | 0 |  | 0 |  | 0 |  | 0 | 1 | 0
50 |  |  | J5 | RPi-GPIO40 | PinSocket_2x20_P2.54mm_Vertical | 1 | 0.8 | 0 | 0 |  | 0 |  | 0 |  | 0 |  | 0 |  | 0 | 1 | 0.8 |  | 0
51 |  |  | J6 | I2C Disp | PinSocket_1x04_P2.54mm_Vertical | 1 | 0.05 | 0 | 0 |  | 0 |  | 0 |  | 0 |  | 0 |  | 0 | 1 | 0.05 |  | 0
52 |  |  | J7 | KEY-PADDLE-1_8 | CUI_SJ1-3534NG-audio-jack | 1 | 1.5 | 0 | 0 |  | 0 | 1 | 1.5 |  | 0 |  | 0 |  | 0 |  | 0 |  | 0
53 |  |  | PCB | MuKOB IF MkIV | PCBWay | 1 | 6.5 | 1 | 6.5 |  | 0 |  | 0 |  | 0 |  | 0 |  | 0 |  | 0 |  | 0
54 |  |  | Base | Acrylic | Send-Cut-Send Laser Cut | 1 | 2 | 1 | 2 |  | 0 |  | 0 |  | 0 |  | 0 |  | 0 |  | 0 |  | 0
55 |  |  | Shield | Altoids Tin | (Modifications) | 1 | 2 | 1 | 2 |  | 0 |  | 0 |  | 0 |  | 0 |  | 0 |  | 0 |  | 0
56 |  |  | Screws & Spacers |  | 8 Screws, 4 Alum Spacers, 4 Nylon Spacers (kit) | 1 | 3 | 1 | 3 |  | 0 |  | 0 |  | 0 |  | 0 |  | 0 |  | 0 |  | 0
 |  |  |  |  | Totals | 79 |  | 52 | 27.439999999999998 | 1 | 1.8 | 1 | 1.5 | 2 | 1 | 10 | 3.97 | 3 | 3.7 | 2 | 0.85000000000000009 | 7 | 1
 |  |  |  | 'Full' >>> | Base + 1/4" Key Jack + Sndr Pwr + L/MS + Test Key |  | 37.71 |  | 27.239999999999995 |  | 1.8 |  |  |  | 1 |  | 3.97 |  | 3.7
 |  |  |  | 'KOB' >>> | Base + Sndr Pwr |  | 28.239999999999995 |  | 27.239999999999995 |  |  |  |  |  | 1

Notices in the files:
hw/MK-CommAdapter.kicad_pcb:
Copyright 2024 AESilky
hw/MK-JackAdapter.kicad_pcb:
MKJA v1.1 Copyright 2024 AESilky
hw/MK-KS-MkII.kicad_pcb:
Copyright AESilky 2023-24
Copyright 2023-24 AESilky
hw/MK-KS-MkV.kicad_pcb:
Copyright 2023-25 AESilky
hw/MuKOB.kicad_sch:
Ref: PicoW VGA_SD_AUD; (c) 2022 Raspberry Pi Ltd
